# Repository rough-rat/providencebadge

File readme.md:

# Providencebadge

## License

This repository contains three separately licensed things:

### Hardware — CERN-OHL-P v2

Copyright © 2026 CritBit.

The electronic design (schematics, PCB layout, routing, and the other design
files in this repository, excluding the artwork and firmware described below) is Open
Hardware, licensed under the CERN Open Hardware Licence Version 2 - Permissive.
You may redistribute and modify it under the terms of the
[CERN-OHL-P v2](LICENSES/CERN-OHL-P-2.0.txt) (https://ohwr.org/cern_ohl_p_v2.txt).

It is distributed WITHOUT ANY EXPRESS OR IMPLIED WARRANTY, INCLUDING OF
MERCHANTABILITY, SATISFACTORY QUALITY AND FITNESS FOR A PARTICULAR PURPOSE.
Please see the CERN-OHL-P v2 for applicable conditions.

### Artwork — CC BY-NC-SA 4.0

Copyright © 2026 @weasel.

The character artwork — the drawings in the `.svg` files and the same graphics
where they appear in the PCB files (silkscreen, copper, solder mask and board
outline) — is licensed under
[Creative Commons Attribution-NonCommercial-ShareAlike 4.0 International](LICENSES/CC-BY-NC-SA-4.0.txt)
(https://creativecommons.org/licenses/by-nc-sa/4.0/).

Because the artwork is part of the board layout, a badge manufactured from
these files as-is includes it, so the non-commercial and share-alike conditions
apply to such badges. The CERN-OHL-P terms apply on their own only to the design with the
artwork removed or replaced.

### Firmware — MIT

Copyright © 2026 CritBit.

The firmware in [`fw/`](fw/) is licensed under the [MIT License](LICENSES/MIT.txt).

### Fan work disclaimer

This is an unofficial, non-commercial fan work depicting a character from
*ULTRAKILL*. *ULTRAKILL* and its characters belong to Arsi "Hakita" Patala and
New Blood Interactive. This project is not affiliated with or endorsed by them,
and the licenses above cover only the original contributions of the authors
named here, not the underlying character.

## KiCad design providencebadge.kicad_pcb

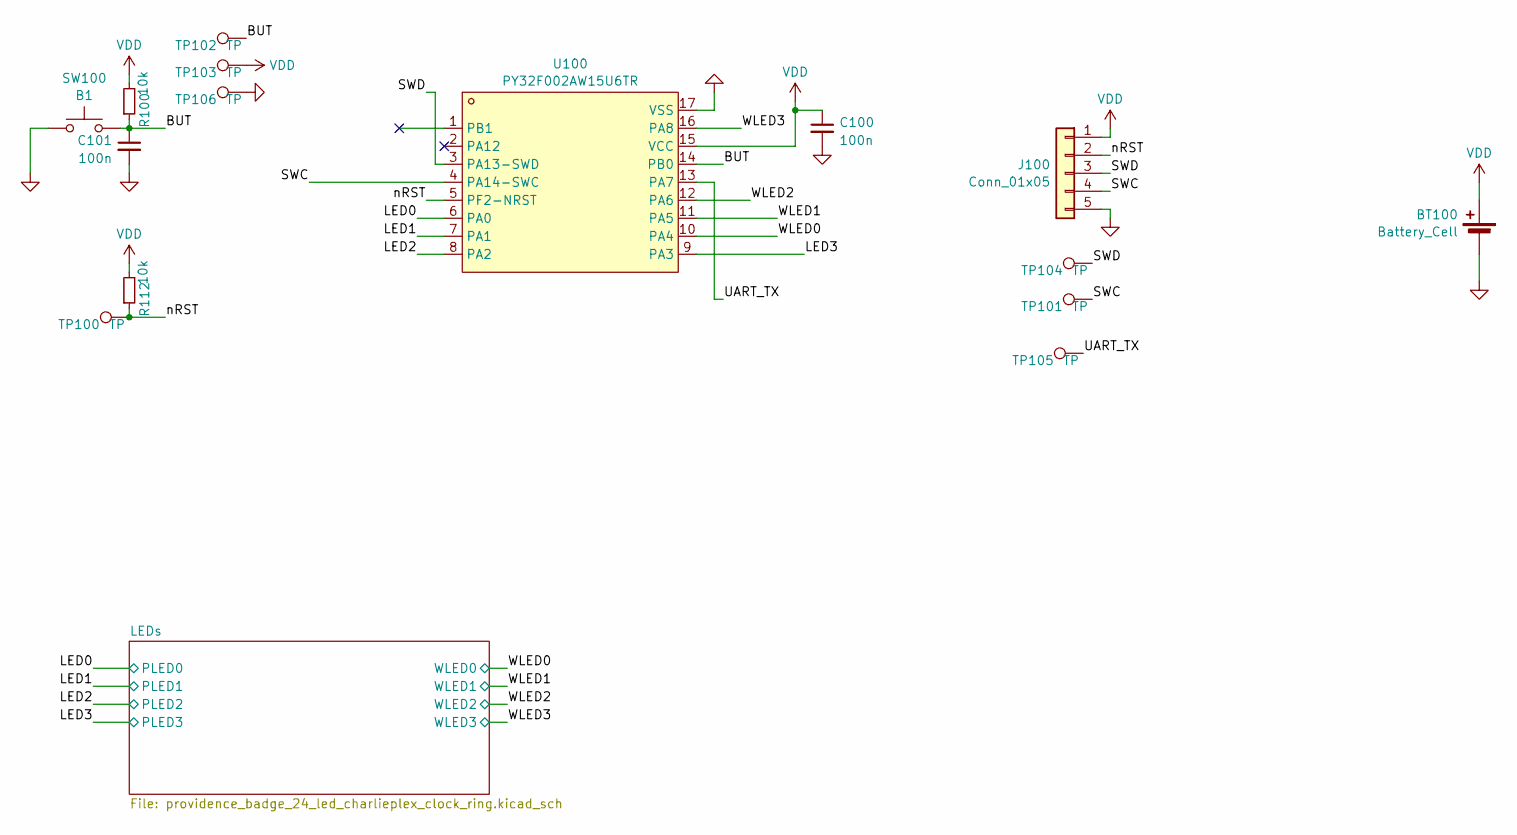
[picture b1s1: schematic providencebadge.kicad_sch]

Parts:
BT100: Battery_Cell; BatteryHolder_Keystone_1060_1x2032; LCSC DNP
C100, C101: 100n; C_0402_1005Metric; LCSC C1525
J100: Conn_01x05; PinHeader_1x05_P1.27mm_Vertical; LCSC DNP
R100, R112: 10k; R_0402_1005Metric; LCSC C25744
SW100: B1; SW_SPST_FSMSM; LCSC DNP
TP100, TP101, TP102, TP103, TP104, TP105, TP106: TP; TestPoint_Pad_D1.0mm; LCSC DNP
U100: PY32F002AW15U6TR; TQFN-16_L3.0-W3.0-P0.50-BL-EP1.7; LCSC C5291740

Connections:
/BUT: C101.1, R100.1, SW100.2, TP102.1 (1_1), U100.14 (PB0)
/LED0: U100.6 (PA0); also elsewhere on the board
/LED1: U100.7 (PA1); also elsewhere on the board
/LED2: U100.8 (PA2); also elsewhere on the board
/LED3: U100.9 (PA3); also elsewhere on the board
/SWC: J100.4, TP101.1 (1_1), U100.4 (PA14-SWC)
/SWD: J100.3, TP104.1 (1_1), U100.3 (PA13-SWD)
/UART_TX: TP105.1 (1_1), U100.13 (PA7)
/WLED0: U100.10 (PA4); also elsewhere on the board
/WLED1: U100.11 (PA5); also elsewhere on the board
/WLED2: U100.12 (PA6); also elsewhere on the board
/WLED3: U100.16 (PA8); also elsewhere on the board
/nRST: J100.2, R112.1, TP100.1 (1_1), U100.5 (PF2-NRST)
GND: BT100.2 (-), C100.2, C101.2, J100.5, SW100.1, TP106.1 (1_1), U100.17 (VSS)
VDD: BT100.1 (+), C100.1, J100.1, R100.2, R112.2, TP103.1 (1_1), U100.15 (VCC)

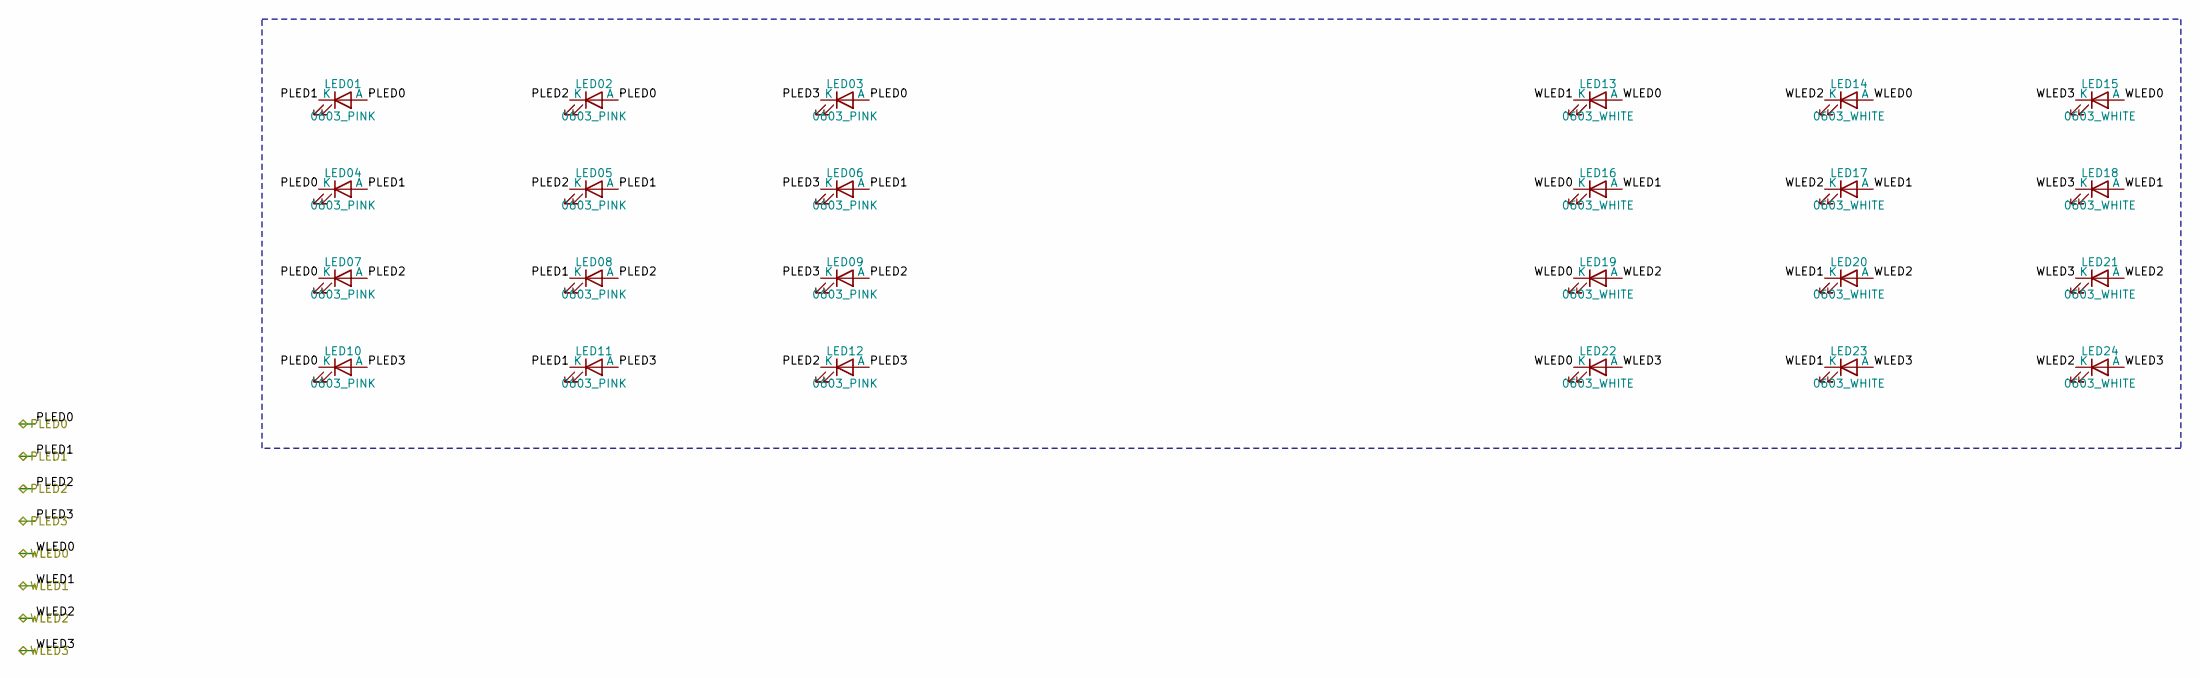
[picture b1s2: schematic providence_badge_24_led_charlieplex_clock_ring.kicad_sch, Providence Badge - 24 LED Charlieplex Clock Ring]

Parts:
LED01, LED02, LED03, LED04, LED05, LED06, LED07, LED08, LED09, LED10, LED11, LED12: 0603_PINK; SideLed_L1.7-W1.1
LED13, LED14, LED15, LED16, LED17, LED18, LED19, LED20, LED21, LED22, LED23, LED24: 0603_WHITE; SideLed_L1.7-W1.1

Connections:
/LED0: LED01.2 (A), LED02.2 (A), LED03.2 (A), LED04.1 (K), LED07.1 (K), LED10.1 (K); also elsewhere on the board
/LED1: LED01.1 (K), LED04.2 (A), LED05.2 (A), LED06.2 (A), LED08.1 (K), LED11.1 (K); also elsewhere on the board
/LED2: LED02.1 (K), LED05.1 (K), LED07.2 (A), LED08.2 (A), LED09.2 (A), LED12.1 (K); also elsewhere on the board
/LED3: LED03.1 (K), LED06.1 (K), LED09.1 (K), LED10.2 (A), LED11.2 (A), LED12.2 (A); also elsewhere on the board
/WLED0: LED13.2 (A), LED14.2 (A), LED15.2 (A), LED16.1 (K), LED19.1 (K), LED22.1 (K); also elsewhere on the board
/WLED1: LED13.1 (K), LED16.2 (A), LED17.2 (A), LED18.2 (A), LED20.1 (K), LED23.1 (K); also elsewhere on the board
/WLED2: LED14.1 (K), LED17.1 (K), LED19.2 (A), LED20.2 (A), LED21.2 (A), LED24.1 (K); also elsewhere on the board
/WLED3: LED15.1 (K), LED18.1 (K), LED21.1 (K), LED22.2 (A), LED23.2 (A), LED24.2 (A); also elsewhere on the board

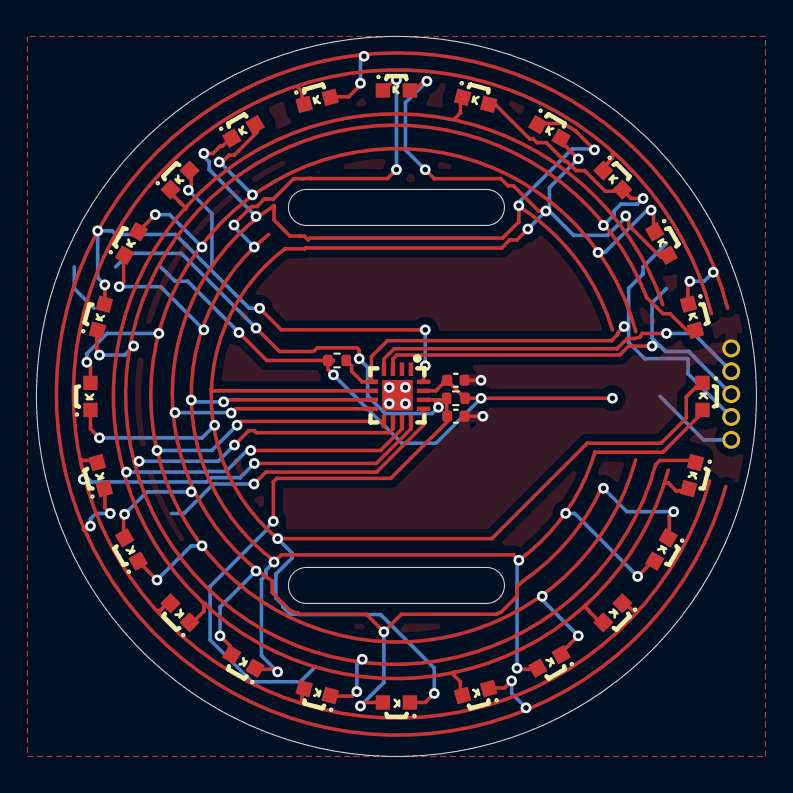
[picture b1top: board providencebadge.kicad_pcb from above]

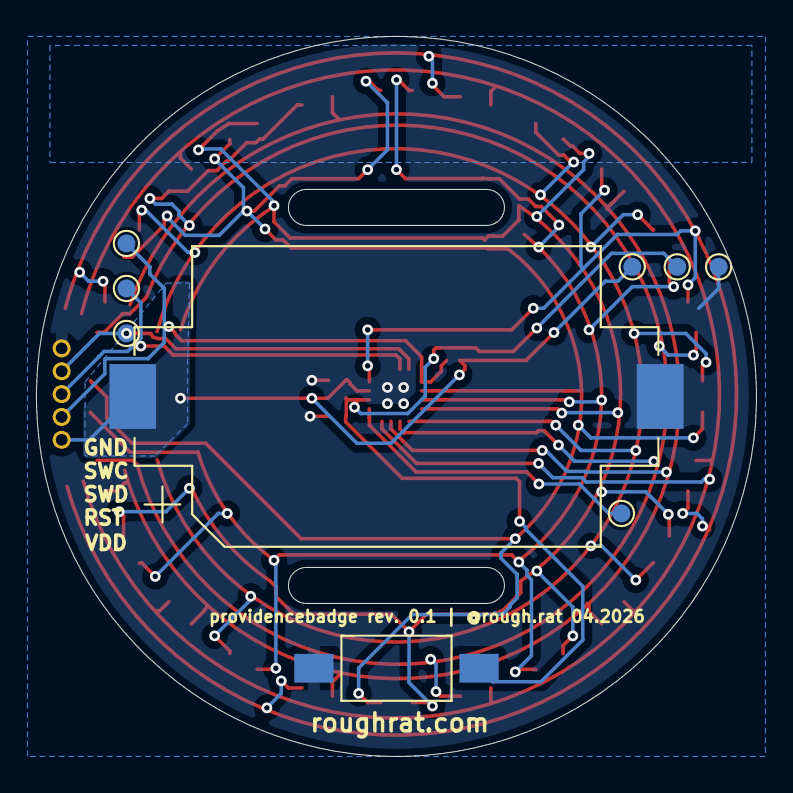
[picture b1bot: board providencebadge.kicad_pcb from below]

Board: 2 copper layers, 40.0 x 40.0 mm, 39 parts (9 on the bottom side), 15 nets.

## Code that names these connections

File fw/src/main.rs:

#![no_std]
#![no_main]
#![feature(impl_trait_in_assoc_type)]

use cortex_m::peripheral::SCB;
use cortex_m_rt::{exception, ExceptionFrame};
use embassy_executor::Spawner;
use embassy_time::{Duration, Instant, Timer};

use py32_hal::gpio::{AnyPin, Flex, Input, Pin, Pull, Speed};

use py32_hal::rcc::Sysclk;
use py32_hal::time::Hertz;
use defmt::*;
use py32_hal::Peripheral;
use {defmt_rtt as _, panic_halt as _};

mod bat;
mod sleep;

const AWAKE_TIMEOUT: Duration = Duration::from_secs(60 * 60);
const BUTTON_DEBOUNCE: Duration = Duration::from_millis(40);
const FLASH_RESCUE_WINDOW: Duration = Duration::from_secs(5);
const LED_SCAN_HOLD_US: u64 = 1_200;
const CROSS_STEP: Duration = Duration::from_millis(2_000 / 12);
const WHITE_HOLD: Duration = Duration::from_secs(2);
const DARK_HOLD: Duration = Duration::from_secs(6);

const PINK_LAYOUT_TO_OFFSET: [usize; 12] = [3, 6, 9, 0, 7, 10, 1, 4, 11, 2, 5, 8];
const WHITE_LAYOUT_TO_OFFSET: [usize; 12] = PINK_LAYOUT_TO_OFFSET;
const OFFSET_TO_ROW_COL: [(usize, usize); 12] = [
    (0, 1),
    (0, 2),
    (0, 3),
    (1, 0),
    (1, 2),
    (1, 3),
    (2, 0),
    (2, 1),
    (2, 3),
    (3, 0),
    (3, 1),
    (3, 2),
];

const WHITE_TEST_LEDS: [usize; 4] = [14, 15, 20, 21];

struct DirectCharlieBank<'a, const PIN_COUNT: usize> {
    pin_list: [Flex<'a>; PIN_COUNT],
}

impl<'a, const PIN_COUNT: usize> DirectCharlieBank<'a, PIN_COUNT> {
    fn new(pin_list: [AnyPin; PIN_COUNT]) -> Self {
        let gpio_list = core::array::from_fn(|i| unsafe {
            Flex::new(pin_list[i].clone_unchecked())
        });

        let mut bank = Self {
            pin_list: gpio_list,
        };
        bank.all_tri_state();
        bank
    }

    fn all_tri_state(&mut self) {
        for pin in self.pin_list.iter_mut() {
            pin.set_as_input(Pull::None);
        }
    }

    fn all_analog(&mut self) {
        for pin in self.pin_list.iter_mut() {
            pin.set_as_analog();
        }
    }

    fn set_masks(&mut self, high_mask: u8, low_mask: u8) {
        self.all_tri_state();

        for i in 0..PIN_COUNT {
            let mask = 1 << i;
            if high_mask & mask != 0 {
                self.pin_list[i].set_high();
            } else if low_mask & mask != 0 {
                self.pin_list[i].set_low();
            }
        }

        for i in 0..PIN_COUNT {
            let mask = 1 << i;
            if (high_mask | low_mask) & mask != 0 {
                self.pin_list[i].set_as_output(Speed::VeryHigh);
            }
        }
    }

    fn set_led_by_offset(&mut self, offset: usize) {
        let (row_low, col_high) = OFFSET_TO_ROW_COL[offset];
        self.set_masks(1 << col_high, 1 << row_low);
    }
}

async fn wait_for_button_release(button: &Input<'_>) {
    while button.is_low() {
        Timer::after_millis(10).await;
    }
    Timer::after(BUTTON_DEBOUNCE).await;
}

async fn pressed_after_debounce(button: &Input<'_>) -> bool {
    if button.is_high() {
        return false;
    }

    Timer::after(BUTTON_DEBOUNCE).await;
    button.is_low()
}

async fn flash_rescue_window(button: &Input<'_>) {
    let deadline = Instant::now() + FLASH_RESCUE_WINDOW;

    while Instant::now() < deadline {
        if button.is_low() {
            info!("button held during rescue window; staying awake");
            wait_for_button_release(button).await;
            return;
        }

        Timer::after_millis(25).await;
    }
}

fn pink_offset(layout_index: usize) -> usize {
    PINK_LAYOUT_TO_OFFSET[layout_index]
}

fn white_offset(layout_index: usize) -> usize {
    WHITE_LAYOUT_TO_OFFSET[layout_index - 12]
}

async fn render_led_sets_for(
    red: &mut DirectCharlieBank<'_, 4>,
    white: &mut DirectCharlieBank<'_, 4>,
    button: &Input<'_>,
    red_offsets: &[usize],
    white_offsets: &[usize],
    duration: Duration,
) -> bool {
    let deadline = Instant::now() + duration;
    let scan_count = usize::max(red_offsets.len(), white_offsets.len());

    while Instant::now() < deadline {
        if pressed_after_debounce(button).await {
            return true;
        }

        if scan_count == 0 {
            Timer::after_millis(10).await;
            continue;
        }

        for scan_index in 0..scan_count {
            if let Some(offset) = red_offsets.get(scan_index % red_offsets.len().max(1)) {
                red.set_led_by_offset(*offset);
            } else {
                red.all_tri_state();
            }

            if let Some(offset) = white_offsets.get(scan_index % white_offsets.len().max(1)) {
                white.set_led_by_offset(*offset);
            } else {
                white.all_tri_state();
            }

            Timer::after_micros(LED_SCAN_HOLD_US).await;
            red.all_tri_state();
            white.all_tri_state();
        }
    }

    false
}

async fn render_dark_for(button: &Input<'_>, duration: Duration) -> bool {
    let deadline = Instant::now() + duration;

    while Instant::now() < deadline {
        if pressed_after_debounce(button).await {
            return true;
        }

        Timer::after_millis(20).await;
    }

    false
}

async fn run_target_animation_once(
    red: &mut DirectCharlieBank<'_, 4>,
    white: &mut DirectCharlieBank<'_, 4>,
    button: &Input<'_>,
) -> bool {
    for step in 0..12 {
        let cross = [
            pink_offset(step),
            pink_offset((step + 3) % 12),
            pink_offset((step + 6) % 12),
            pink_offset((step + 9) % 12),
        ];

        if render_led_sets_for(red, white, button, &cross, &[], CROSS_STEP).await {
            return true;
        }
    }

    let white_leds = [
        white_offset(WHITE_TEST_LEDS[0]),
        white_offset(WHITE_TEST_LEDS[1]),
        white_offset(WHITE_TEST_LEDS[2]),
        white_offset(WHITE_TEST_LEDS[3]),
    ];

    if render_led_sets_for(red, white, button, &[], &white_leds, WHITE_HOLD).await {
        return true;
    }

    red.all_tri_state();
    white.all_tri_state();
    render_dark_for(button, DARK_HOLD).await
}

#[embassy_executor::main]
async fn main(_spawner: Spawner) {
    info!("Hello World!");

    let mut cfg: py32_hal::Config = Default::default();
    cfg.rcc.hsi = Some(Hertz::mhz(24));
    cfg.rcc.sys = Sysclk::HSI;
    let p = py32_hal::init(cfg);

    // _spawner.spawn(bat::run_bat_monitor(p.ADC)).unwrap();

    let button = Input::new(p.PB0, Pull::None);

    let red_pins = [
        p.PA0.degrade(),
        p.PA1.degrade(),
        p.PA2.degrade(),
        p.PA3.degrade(),
    ];

    let white_pins = [
        p.PA4.degrade(),
        p.PA5.degrade(),
        p.PA6.degrade(),
        p.PA8.degrade(),
    ];
    
    let mut red = DirectCharlieBank::new(red_pins);
    let mut white = DirectCharlieBank::new(white_pins);

    red.all_analog();
    white.all_analog();
    info!("flash rescue window");
    flash_rescue_window(&button).await;

    info!("entering initial stop mode");
    sleep::enter_stop_mode();
    wait_for_button_release(&button).await;
    info!("awake");

    loop {
        let wake_deadline = Instant::now() + AWAKE_TIMEOUT;

        while Instant::now() < wake_deadline {
            if run_target_animation_once(&mut red, &mut white, &button).await {
                info!("button requested stop");
                wait_for_button_release(&button).await;
                break;
            }
        }

        info!("entering stop mode");
        red.all_analog();
        white.all_analog();
        sleep::enter_stop_mode();
        wait_for_button_release(&button).await;
        info!("awake");
    }
}

//conserve flash space with the non-handler
#[exception]
unsafe fn HardFault(_frame: &ExceptionFrame) -> ! {
    SCB::sys_reset()
}

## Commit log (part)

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2026-04-07 MACHINE, GIT ADD NOW
